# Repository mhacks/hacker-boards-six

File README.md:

MHacks Six Hacker Boards
============
This repository contains the support files for the MHacks 6 Hacker Boards, presented at the Intro to Hardware Workshop ([presentation can be found here](https://docs.google.com/presentation/d/15O3TXqOf3Xi9S6ba83HRF5j0ccdkGcIPRQTYAptkbrs/edit#slide=id.gdf724c5d4_0_47)). In the hardware folder is copies of the Eagle schematic and board layout for the board given to participants, and in the firmware folder is the library to simplify working with the board's LEDs, button, and potentiometer/knob - also called "peripherals".

The MHacks Six Hacker Board. You like it? You should have come to the MHacks Six Intro to Hardware Workshop!

###How to Install the Library
* Inside of the Arduino IDE, go to Sketch->Import Library->Add Library.
* Choose the *HackerBoard* folder inside of the firmware folder.
* The Arduino IDE handles the rest!
* Be sure to check out the example animation (File->Examples->HackerBoard) if you're unsure how to work with the library, or what to do!

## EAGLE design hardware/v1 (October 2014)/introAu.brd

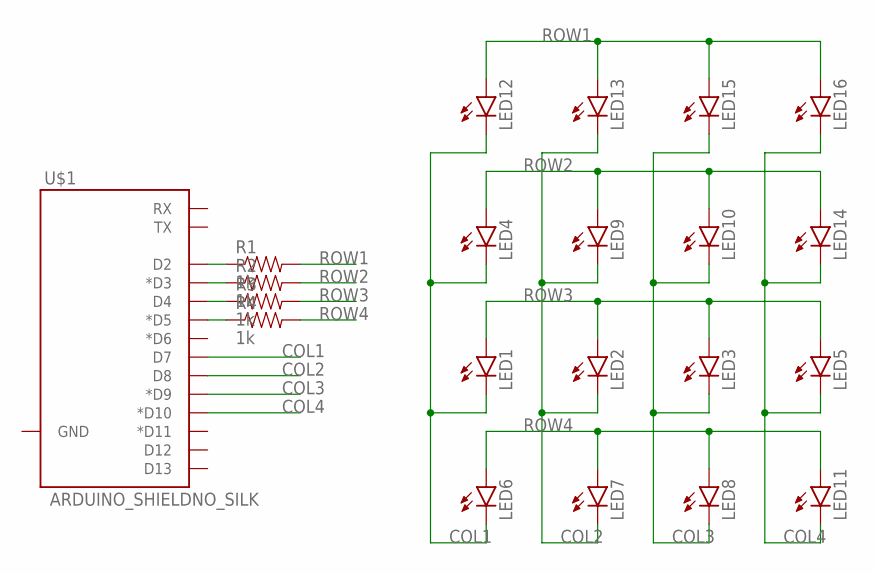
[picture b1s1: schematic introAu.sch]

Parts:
LED1, LED2, LED3, LED4, LED5, LED6, LED7, LED8, LED9, LED10, LED11, LED12, LED13, LED14, LED15, LED16: LED5MM
R1, R2, R3, R4: 1k; AXIAL-0.3EZ
U$1: ARDUINO_SHIELDNO_SILK; DUEMILANOVE_VIAS

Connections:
COL1: LED1.K (C), LED4.K (C), LED6.K (C), LED12.K (C), U$1.D7
COL2: LED2.K (C), LED7.K (C), LED9.K (C), LED13.K (C), U$1.D8
COL3: LED3.K (C), LED8.K (C), LED10.K (C), LED15.K (C), U$1.D9 (*D9)
COL4: LED5.K (C), LED11.K (C), LED14.K (C), LED16.K (C), U$1.D10 (*D10)
unnamed: R1.P$1 (1), U$1.D2
unnamed: R2.P$1 (1), U$1.D3 (*D3)
unnamed: R3.P$1 (1), U$1.D4
unnamed: R4.P$1 (1), U$1.D5 (*D5)
ROW1: LED12.A, LED13.A, LED15.A, LED16.A, R1.P$2 (2)
ROW2: LED4.A, LED9.A, LED10.A, LED14.A, R2.P$2 (2)
ROW3: LED1.A, LED2.A, LED3.A, LED5.A, R3.P$2 (2)
ROW4: LED6.A, LED7.A, LED8.A, LED11.A, R4.P$2 (2)

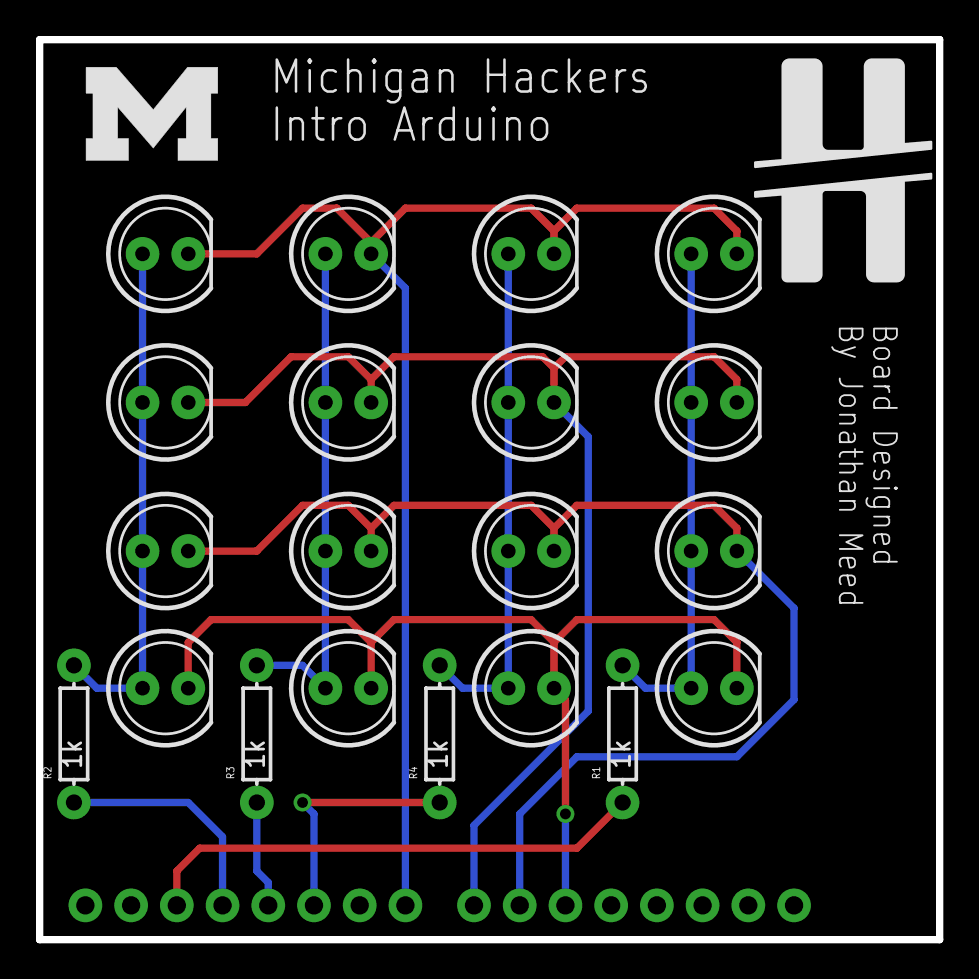
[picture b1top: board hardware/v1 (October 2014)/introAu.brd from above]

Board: 2 copper layers, 50.0 x 50.0 mm, 23 parts (0 on the bottom side), 12 nets.

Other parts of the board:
U$2: SMALL-M
U$3: SMALL-MH

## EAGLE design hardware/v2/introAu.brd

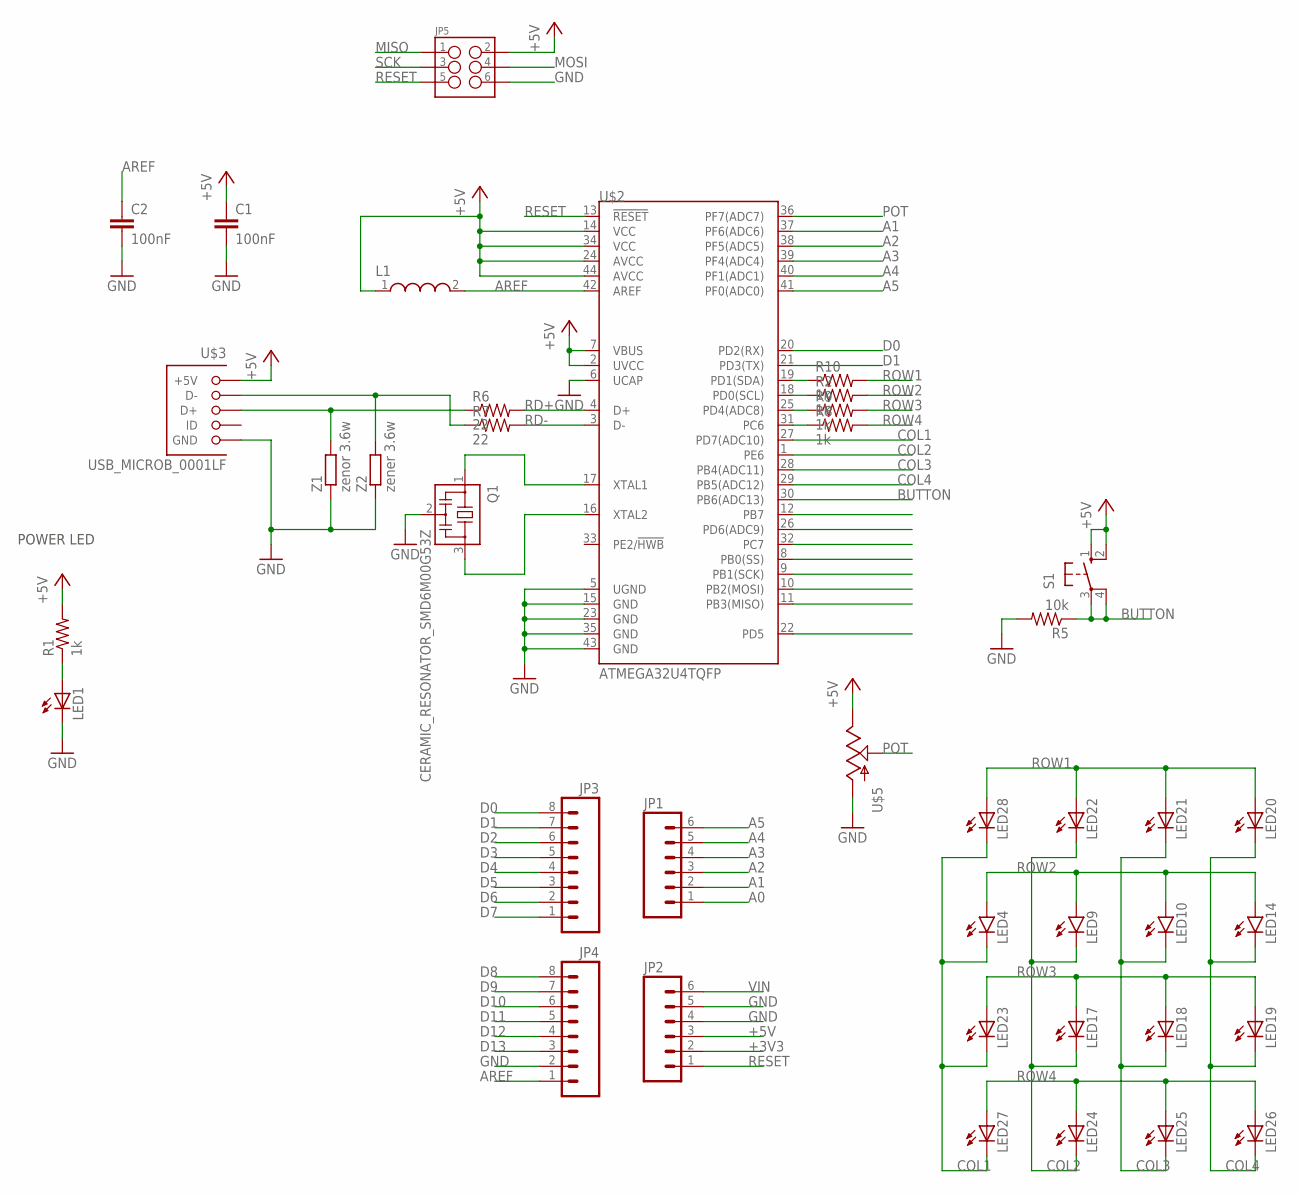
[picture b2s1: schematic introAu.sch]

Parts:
C1, C2: 100nF; C0805
JP1, JP2: M06SMD-STRAIGHT-COMBO; 1X06_SMD_STRAIGHT_COMBO
JP3, JP4: M08SMD-COMBO; 1X08_SMD_COMBINED
JP5: M03X22X3_SILK_SM; 2X3
L1: WE-CBF_0805(WB/HS); WE-CBF_0805(W=3.0)
LED1, LED17, LED18, LED19, LED20, LED21, LED22, LED23, LED24, LED25, LED26, LED27, LED28: LEDCHIPLED_0805; CHIPLED_0805
LED4, LED9, LED10, LED14: LED5MM
Q1: CERAMIC_RESONATOR_SMD6M00G53Z; CERAMIC_RESONATOR_SMD
R1, R8, R9, R10: 1k; R0805
R2: 1k; AXIAL-0.3EZ
R5: 10k; AXIAL-0.3EZ
R6, R7: 22; R0805
S1: TACT_BUTTON; B3F-10XX
U$2: ATMEGA32U4TQFP; SPARKFUN-DIGITALIC_TQFP44
U$3: USB_MICROB_0001LF; USB_MICROB_CHEAPER
U$5: POT; ALPS_POT
Z1: zenor 3.6w; R0603
Z2: zener 3.6w; R0603

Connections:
+3V3: JP2.2
+5V: C1.1, JP2.3, JP5.2, L1.1, R1.2, S1.1 (S), S1.2 (S1), U$2.2 (UVCC), U$2.7 (VBUS), U$2.14 (VCC), U$2.24 (AVCC), U$2.34 (VCC), U$2.44 (AVCC), U$3.P$1 (+5V), U$5.P$1 (E)
A0: JP1.1
A1: JP1.2, U$2.37 (PF6(ADC6))
A2: JP1.3, U$2.38 (PF5(ADC5))
A3: JP1.4, U$2.39 (PF4(ADC4))
A4: JP1.5, U$2.40 (PF1(ADC1))
A5: JP1.6, U$2.41 (PF0(ADC0))
AREF: C2.1, JP4.1, L1.2, U$2.42 (AREF)
BUTTON: R5.P$1 (1), S1.3, S1.4 (P1), U$2.30 (PB6(ADC13))
COL1: LED4.K (C), LED23.C, LED27.C, LED28.C, U$2.27 (PD7(ADC10))
COL2: LED9.K (C), LED17.C, LED22.C, LED24.C, U$2.1 (PE6)
COL3: LED10.K (C), LED18.C, LED21.C, LED25.C, U$2.28 (PB4(ADC11))
COL4: LED14.K (C), LED19.C, LED20.C, LED26.C, U$2.29 (PB5(ADC12))
D0: JP3.8, U$2.20 (PD2(RX))
D1: JP3.7, U$2.21 (PD3(TX))
D2: JP3.6
D3: JP3.5
D4: JP3.4
D5: JP3.3
D6: JP3.2
D7: JP3.1
D8: JP4.8
D9: JP4.7
D10: JP4.6
D11: JP4.5, U$2.12 (PB7)
D12: JP4.4, U$2.26 (PD6(ADC9))
D13: JP4.3, U$2.32 (PC7)
D14: U$2.11 (PB3(MISO))
D15: U$2.9 (PB1(SCK))
D16: U$2.10 (PB2(MOSI))
D17: U$2.8 (PB0(SS))
GND: C1.2, C2.2, JP2.4, JP2.5, JP4.2, JP5.6, LED1.C, Q1.2, R5.P$2 (2), U$2.5 (UGND), U$2.6 (UCAP), U$2.15 (GND), U$2.23 (GND), U$2.35 (GND), U$2.43 (GND), U$3.P$4 (GND), U$5.P$3 (A), Z1.1, Z2.1
MISO: JP5.1
MOSI: JP5.4
unnamed: R10.1, U$2.19 (PD1(SDA))
unnamed: R2.P$1 (1), U$2.18 (PD0(SCL))
unnamed: R9.1, U$2.25 (PD4(ADC8))
unnamed: R8.1, U$2.31 (PC6)
unnamed: Q1.3, U$2.16 (XTAL2)
unnamed: Q1.1, U$2.17 (XTAL1)
unnamed: R7.1, U$3.P$2 (D-), Z2.2
unnamed: R6.1, U$3.P$3 (D+), Z1.2
unnamed: LED1.A, R1.1
POT: U$2.36 (PF7(ADC7)), U$5.P$2 (S)
RD+: R6.2, U$2.4 (D+)
RD-: R7.2, U$2.3 (D-)
RESET: JP2.1, JP5.5, U$2.13 (!RESET)
ROW1: LED20.A, LED21.A, LED22.A, LED28.A, R10.2
ROW2: LED4.A, LED9.A, LED10.A, LED14.A, R2.P$2 (2)
ROW3: LED17.A, LED18.A, LED19.A, LED23.A, R9.2
ROW4: LED24.A, LED25.A, LED26.A, LED27.A, R8.2
SCK: JP5.3
TX: U$2.22 (PD5)
VIN: JP2.6

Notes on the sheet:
POWER LED

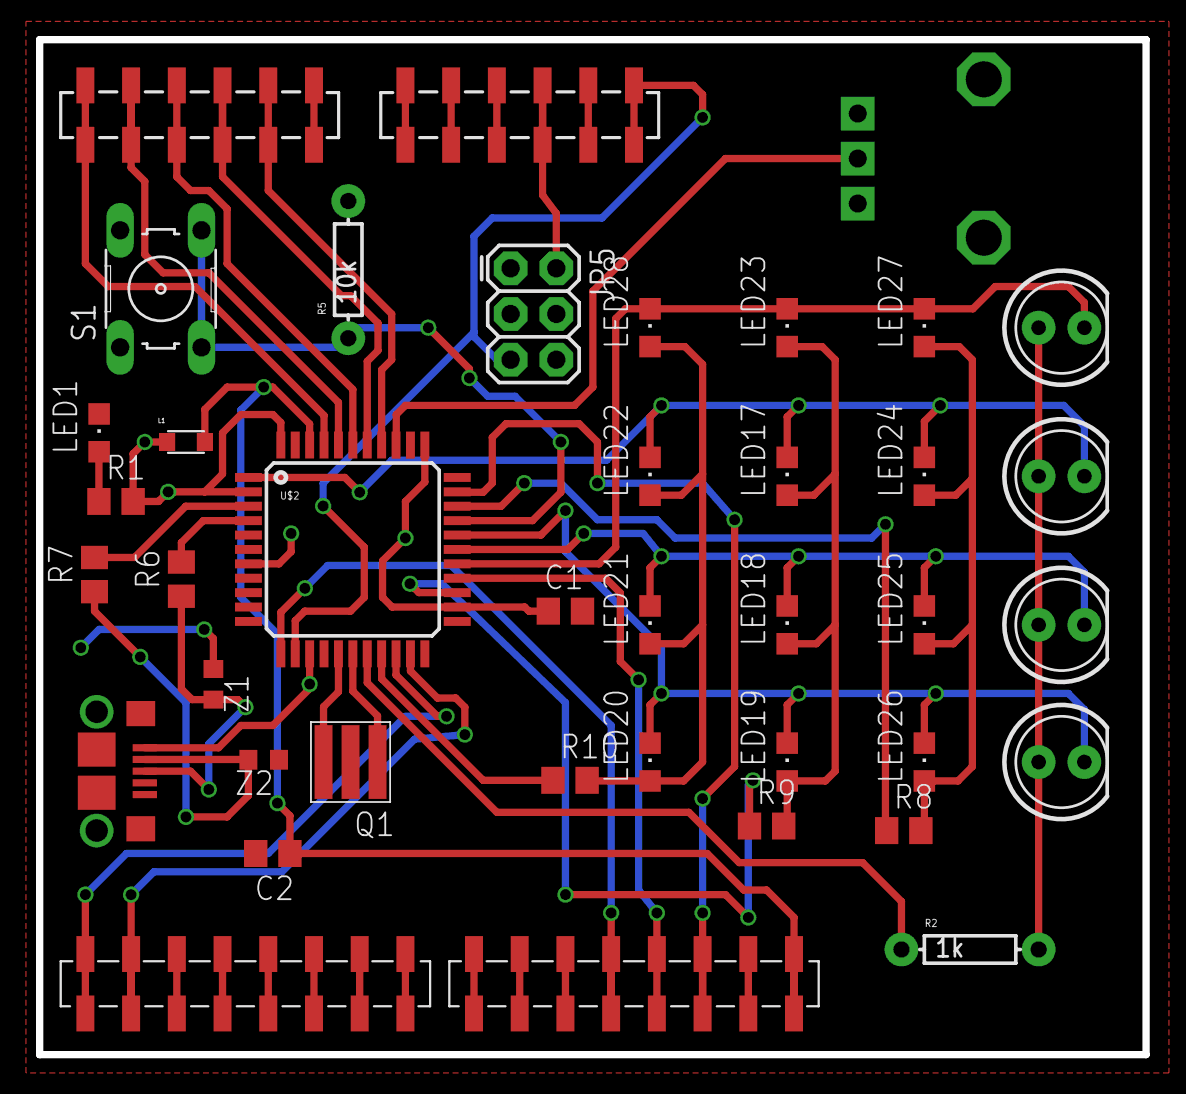
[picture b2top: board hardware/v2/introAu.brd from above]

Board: 2 copper layers, 61.5 x 56.4 mm, 40 parts (0 on the bottom side), 35 nets.

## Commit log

2015-09-15 Initial commit for MHacks Six Hacker Bards, imported from michiganhackers/introarduino

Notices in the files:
parts and their libraries:
SparkFun-Boards: Licensing: Creative Commons ShareAlike 4.0 International - https://creativecommons.org/licenses/by-sa/4.0
SparkFun-Electromechanical: Licensing: CC v3.0 Share-Alike You are welcome to use this library for commercial purposes.
